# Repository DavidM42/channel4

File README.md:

# channel4

Analog broadcast television straight out of an ESP8266 pin, set up for black and white PAL TVs.

> ## This is cnlohr's work
>
> channel4 is a fork of **[cnlohr/channel3](https://github.com/cnlohr/channel3)** by Charles Lohr.
> The idea, the RF trick, the firmware, the 3D engine and the web interface are all his, and they are great.
> PAL line timing was also already in channel3, contributed there.
>
> This fork only adapts that work so it gives a solid picture on European black and white PAL sets, adds a few options around that, and explains how to build and flash it on a current Mac or Linux machine.
> The changes in this fork were made with the help of an AI coding assistant.
>
> If you have an NTSC TV, or you want color, use the original.

Solder a wire to the RX pin, flash the board, tune an old TV to channel E4 and watch a 3D demo that an ESP8266 is transmitting by toggling one pin.

## What is different from channel3

- **It broadcasts on European channel E4** (62.5 MHz) instead of US channel 3 (61.25 MHz), hence the name.
- **Black and white mode.** `MONOCHROME` leaves out all NTSC color information. The colors become clean shades of gray instead of hatching.
- **Optional bright border** for TVs that show dark screens as gray.
- **A steady PAL picture.** `NO_INTERLACE` stops the picture from jumping up and down by half a line, see [No interlacing](#no-interlacing).
- **Text from Home Assistant.** A text screen that you fill over WiFi, with a ready-made Home Assistant package.
- **A pause for the TV signal while a screen is sent.** The TV signal slows the board's WiFi down so much that a full screen can take a minute. With the pause it takes a few seconds, see [Faster screens](#faster-screens).
- **It stays on your WiFi.** channel3 switches back to its own access point at every start. This fork does not.
- **A relay that follows the screen.** With `RELAY_GPIO` a pin goes high whenever something is shown, for example to switch the TV on, see [A relay](#a-relay).
- **A silent start.** With `START_SILENT` the TV signal only starts when something asks for a screen, and a command stops it again, see [Signal only when needed](#signal-only-when-needed).
- **Updates over WiFi that check their work.** New firmware goes on over the network, is verified and only then takes over, see [Updating over WiFi](#updating-over-wifi).
- **A filter for the antenna pin.** The TV signal jams the board's own WiFi. Two small parts at the pin fix most of that, see [WiFi and the TV signal](#wifi-and-the-tv-signal).
- **PAL, black and white and no interlacing are switched on by default** in `user.cfg`.
- **A cable instead of an antenna.** A small board for the D1 Mini feeds the signal into the antenna socket of the TV, see [By cable instead of an antenna](#by-cable-instead-of-an-antenna).
- **Setup, build and flash instructions** for macOS and Linux, below.

Everything else, including the web interface and the demo screens, is channel3.

## What you need

- **An ESP8266 board with USB and 4 MB of flash.** A Wemos D1 Mini is what this was built and tested on.
- **A USB cable that carries data.** Many micro USB cables only charge. If no serial port shows up, try another cable first.
- **A piece of wire** for the antenna, 20 to 30 cm to start with. See [Antenna](#antenna).
- **A 100 ohm resistor and a 10 pF capacitor**, if you want to use WiFi while it broadcasts. See [The filter at the pin](#the-filter-at-the-pin).
- **An analog TV that receives VHF band I** (often labeled VHF-L or VL) in the B/G standard used in most of continental Europe.
- **A Mac or a Linux PC.** macOS on Apple Silicon was used for everything here, including flashing. On Linux the setup and build steps were checked on Ubuntu 24.04. Flashing from Linux was not tried, it is the same esptool command.

## Setup, build and flash

The whole thing is six steps. Steps 1 and 2 are only needed once.

### 1. Install the tools

You need `git`, `make` and `esptool` in version 4.8.1.

**macOS** (with [Homebrew](https://brew.sh))

```sh
xcode-select --install                 # git and make, skip if you have them
brew install pipx
pipx install esptool==4.8.1
pipx ensurepath                        # then open a new terminal
softwareupdate --install-rosetta       # Apple Silicon only, the compiler is an Intel program
```

On a Mac you also need the driver for the USB serial chip on the board. The Wemos D1 Mini uses a CH340, and its maker WCH has the driver here: https://www.wch-ic.com/downloads/CH34XSER_MAC_ZIP.html
Download it, run the installer, and allow it if macOS asks you to in System Settings under Privacy & Security. On the Mac this was built on, the board did not show up as a serial port before the driver was installed.

Boards with a different USB serial chip (a CP2102 for example) need that chip's driver instead.

**Linux** (Debian, Ubuntu and relatives, on a 64-bit Intel or AMD PC)

```sh
sudo apt-get install git make gcc python3 pipx wget
pipx install esptool==4.8.1
pipx ensurepath                        # then open a new terminal
sudo usermod -aG dialout $USER         # lets you use the serial port, log out and in again afterwards
```

Linux needs no driver for the CH340, it comes with the kernel.

Check that it worked. This should print `4.8.1`:

```sh
esptool.py version
```

The version matters. `brew install esptool` and a plain `pipx install esptool` give you esptool 5, and the build stops there with `Specify the --chip argument`. If you need esptool 5 for other things, see [Troubleshooting](#troubleshooting).

### 2. Get the compiler

The ESP8266 needs its own compiler, `xtensa-lx106-elf-gcc`.
Espressif publishes a ready-made one, so there is nothing to build.
Put it in `~/esp8266`:

**macOS**

```sh
mkdir -p ~/esp8266 && cd ~/esp8266
curl -LO https://dl.espressif.com/dl/xtensa-lx106-elf-macos-1.22.0-100-ge567ec7-5.2.0.tar.gz
tar xzf xtensa-lx106-elf-macos-1.22.0-100-ge567ec7-5.2.0.tar.gz
```

**Linux**

```sh
mkdir -p ~/esp8266 && cd ~/esp8266
wget https://dl.espressif.com/dl/xtensa-lx106-elf-linux64-1.22.0-100-ge567ec7-5.2.0.tar.gz
tar xzf xtensa-lx106-elf-linux64-1.22.0-100-ge567ec7-5.2.0.tar.gz
```

Check that it worked. This should print `5.2.0`:

```sh
~/esp8266/xtensa-lx106-elf/bin/xtensa-lx106-elf-gcc -dumpversion
```

### 3. Get the source

```sh
git clone --recursive https://github.com/DavidM42/channel4.git
cd channel4
```

`--recursive` matters. Most of the build lives in a submodule (`esp82xx`), and without it `make` finds nothing to do.
If you already cloned without it, run `git submodule update --init --recursive`.

### 4. Build

Run this in the `channel4` folder:

```sh
make clean ESP_ROOT="$HOME/esp8266" ESP_GCC_VERS=5.2.0 ESPTOOL_PY=esptool.py
make all   ESP_ROOT="$HOME/esp8266" ESP_GCC_VERS=5.2.0 ESPTOOL_PY=esptool.py
```

The three settings tell the build where the compiler from step 2 is, which version it is, and to use the esptool from step 1.

You will see a lot of compiler warnings. That is normal.
It worked if the last line says `Successfully created esp8266 image.` and these two files exist:

```
image.elf-0x00000.bin
image.elf-0x10000.bin
```

Always run `make clean` before `make all` after you change `user.cfg`. The build does not notice changes in that file by itself.

### 5. Flash

Plug the board in and find its serial port.

| | Command | Typical port |
|---|---|---|
| macOS | `ls /dev/cu.*` | `/dev/cu.wchusbserial10` |
| Linux | `ls /dev/ttyUSB*` | `/dev/ttyUSB0` |

If nothing like that is listed, see [Troubleshooting](#troubleshooting). On a Mac the usual reasons are the missing driver from step 1 or a USB cable that only charges.

Put it in a variable so the commands below can be copied as they are:

```sh
PORT=/dev/ttyUSB0      # use your own port here
```

**The first time**, write everything: the firmware, the web page, and the settings area the ESP8266 system software needs.

```sh
esptool.py --port "$PORT" -b 460800 write_flash -fm dio -fs 4MB \
  0x00000  image.elf-0x00000.bin \
  0x10000  image.elf-0x10000.bin \
  0x80000  web/page.mpfs \
  0x3FB000 esp82xx/toolchain/esp_nonos_sdk/bin/blank.bin \
  0x3FC000 esp82xx/toolchain/esp_nonos_sdk/bin/esp_init_data_default_v08.bin \
  0x3FE000 esp82xx/toolchain/esp_nonos_sdk/bin/blank.bin
```

**After that**, when you only rebuilt the firmware, the first two files are enough:

```sh
esptool.py --port "$PORT" -b 460800 write_flash -fm dio -fs 4MB \
  0x00000 image.elf-0x00000.bin \
  0x10000 image.elf-0x10000.bin
```

It worked if every file ends with `Hash of data verified.`

Three things worth knowing:

- **`-fs 4MB` is required.** Without it the firmware believes it has 1 MB of flash and looks for its settings in the wrong place.
- **These addresses are for 4 MB of flash**, which is what a D1 Mini has. `esptool.py --port "$PORT" flash_id` tells you what your board has. Other sizes were not tested here.
- **Use these commands instead of `make burn`.** The make targets leave out `-fs 4MB`, and they report success even when flashing failed.

### 6. Watch TV

1. Connect the wire to the pin labeled **RX** (GPIO3), best through [the filter](#the-filter-at-the-pin), and power the board from any USB supply.
2. Switch the TV to VHF band I (VHF-L, VL) and tune to channel E4, 62.5 MHz. On a set with a tuning wheel, turn slowly through the lower part of the band until the picture appears.
3. Set brightness so the background of a text screen is just black, then contrast so the text is crisp.

If `START_SILENT` is switched on in `user.cfg`, there is no picture until something asks for one. Join the board's WiFi network (see below) and open http://192.168.4.1/d/issue?CD to start the demo, or use the "Set Current" button on the web page.

The board also opens a WiFi network called `ESP_` followed by six characters. Join it and open http://192.168.4.1 for the web interface. Its "NTSC" button lets you freeze the demo on one screen, which makes adjusting the TV much easier.

### Updating over WiFi

Once a board runs this firmware and is on your network, new firmware can go on without USB:

```sh
python3 web/execute_reflash.py 192.168.1.50
```

That sends the two image files from the current folder. `make netburn IP=192.168.1.50`, with the same `ESP_ROOT=...` settings as in step 4, builds first and then does the same.

What happens:

1. It checks that the new firmware can go on this way, and whether the board already runs it.
2. It stops the TV signal, which disturbs the board's WiFi.
3. It puts both images into a spare part of the flash, reads them back and compares.
4. It tells the board to copy them over its firmware. The board checks them once more before it does.
5. It waits for the board to restart and reads its flash back.

Nothing on the board changes before step 4, and `--dry-run` stops before it.

**Step 4 takes about ten seconds. If the power fails in that time, the board does not start any more** and has to be flashed over USB.

The web page and the settings, the WiFi network among them, stay as they are.

## Options

All of these are lines in `user.cfg`. A `#` in front switches a line off.

| Line in `user.cfg` | What it does |
|---|---|
| `OPTS += -DPAL` | PAL timing: 625 lines, 50 fields per second. Off means NTSC. |
| `OPTS += -DMONOCHROME` | Black and white only. No colorburst, and the colors become shades of gray. |
| `OPTS += -DNO_INTERLACE` | PAL only. Draws both fields on the same TV lines, so the picture stands still. See [No interlacing](#no-interlacing). |
| `OPTS += -DFBH=264` | Full height PAL picture, 264 lines instead of 220. The web page then runs out of memory, see [Picture size and memory](#picture-size-and-memory). |
| `OPTS += -DWHITE_BORDER` | Paints the visible area left, right and above the picture bright instead of black. |
| `OPTS += -DBORDER_LEVEL=13` | How bright that border is. Only used together with `WHITE_BORDER`. |
| `OPTS += -DRELAY_GPIO=5` | A relay on that pin, on whenever something is shown. 5 is D1 on a D1 Mini. See [A relay](#a-relay). |
| `OPTS += -DSTART_SILENT` | No TV signal after power-up. It starts with the first text or demo command, see [Signal only when needed](#signal-only-when-needed). |

After changing any of them: `make clean`, `make all`, flash.

### Black and white only

On a black and white TV the NTSC color information only gets in the way. The colors show up as hatching, and the colorburst sits at a different level than black right where some TVs take their black reference.

With `MONOCHROME` there is no colorburst, and colors 0 to 15 become plain grays:

- 0 is black and 10 is white, as before.
- 2 and 8 are still the half black, half white ones that the sharp text uses.
- 3 to 7, 9 and 11 to 15 run from dark to bright.

A single pin can only be on or off, so only a few brightness levels come out clean. On channel E4 that is 8 grays between black and white, and some neighboring color numbers share a gray.

Both color tables live in `tablemaker/broadcast_tables.c`. The option picks one of them.

### No interlacing

A PAL picture is sent as two fields, and a TV draws the second one half a line below the first. channel3 sends the same picture in both, so everything jumps up and down by half a line, 25 times a second. On text that shows as a fine flicker, most of all on horizontal strokes.

With `NO_INTERLACE` the second field starts on a full line instead of half a line later, and the TV draws it on top of the first. Old home computers did the same. A field is then 312 lines instead of 312.5, and nothing of the picture is lost.

It is switched on in `user.cfg`. Take it out if your TV does not hold the picture with it. It only changes PAL, the NTSC signal is as it was.

### Bright border

Many small TVs, most black and white portables among them, do not hold their black level. A mostly dark picture like the text screens comes out as light gray text on a slightly darker gray.

Try the brightness and contrast controls of the TV first. That is usually enough.

If it is not, `WHITE_BORDER` gives the TV something bright to go by on every screen, without taking anything away from the picture. White (`BORDER_LEVEL=10`, the default) works best but glows on a small tube. With `MONOCHROME`, 13 is a light gray and a good place to start.

The lines below the picture always stay black. Bright lines running right up to the vertical sync made the whole picture bounce on the TV this was tried on.

### Picture size and memory

The picture is 220 lines high by default, also for PAL. It sits in the middle of the screen with a black strip above and below, and the text screen has 14 lines.

`FBH=264` fills a PAL screen and gives the text screen 17 lines. The 44 extra lines cost 5 kB of RAM, and the web page needs that memory. Measured with a clean WiFi link (RX pin silent, see [WiFi and the TV signal](#wifi-and-the-tv-signal)), loading the web page the way a browser does:

| Build | Page loads that completed | Lowest free memory |
|---|---|---|
| 220 lines (default) | 8 of 8 | 2.6 kB |
| 264 lines | 0 of 8 | 0.5 kB |

Single small requests, like the text commands from Home Assistant, worked with both: 30 of 30.

To see how much memory is free on your board, open `http://<board>/d/issue?I`. It is the last number.

### Signal only when needed

With `START_SILENT` the RX pin stays silent after power-up. The TV gets nothing, and the board's WiFi is not disturbed by the TV signal.

The signal starts when something asks for a screen, and stops on request:

| What | TV signal |
|---|---|
| `CT`, `CX` (text screen) and `CD` (demo) | on |
| The web page: its "Set Current" button for the screen, and "Upload As" for a color (`CO`, `CV`) | on |
| `CS` | off |

Send the commands as `http://<board>/d/issue?CS` and so on, see [The commands behind it](#the-commands-behind-it).

While the signal is off, no screens are drawn and the demo stands still. It carries on where it stopped, or from its first screen after `CD`. The part that makes the TV lines keeps running, so the picture is there at once when the signal comes on.

Without `START_SILENT` the signal is on from the start, as in channel3. `CS` and the commands that start the signal again work either way.

### A relay

With `RELAY_GPIO` the board switches a relay, for example one that powers the TV. The pin goes high for on.

| What | Relay |
|---|---|
| Every command that shows or changes something: `CT`, `CX`, `CD`, `CH`, `CG`, and `CO` and `CV` from the web page | on |
| `CR` | off |

Nothing else switches it off. `CS` and the pause while a screen is sent only stop the TV signal, the relay stays on through them. After power-up the relay is off with `START_SILENT`, and on without it, because the demo is showing then.

The number is the GPIO, not the label on the board. On a D1 Mini these are free:

| Label | `RELAY_GPIO` |
|---|---|
| D1 | 5 |
| D2 | 4 |
| D5 | 14 |
| D6 | 12 |
| D7 | 13 |

0, 2 and 15 work too, but the board reads those pins when it starts, and a relay on them can keep it from starting. The build stops with a message for any other number.

The pin gives 3.3 V and a few milliamps. That is enough for a relay module with its own transistor or optocoupler, not for a bare relay.

`RELAY_GPIO=5` is switched on in `user.cfg`. With a `#` in front of the line there is no relay, and the pin is left alone.

## Antenna

The antenna is a plain wire on the **RX** pin. For the picture alone that is all you need. If you also want WiFi to work, put [the filter](#the-filter-at-the-pin) between the pin and the wire.

- **Start with 20 to 30 cm**, laid near the TV or its aerial. That is enough across a table or a room.
- **A full quarter wave is about 1.15 m** on channel E4. Only go there if the short wire gives a snowy picture.
- **Do not go longer than you need.** The pin puts out a raw 80 MHz bit stream. Next to the TV channel it also produces copies on other frequencies, one of them around 97.5 MHz in the FM radio band. A longer wire radiates all of them further, and you have no license for any of them. Keep it on your desk.

For other channels, a quarter wave in meters is about 71 divided by the frequency in MHz.

**Keep the wire away from the board's own antenna**, the zigzag trace at the end of the ESP8266 module. The TV signal disturbs the board's WiFi, see [WiFi and the TV signal](#wifi-and-the-tv-signal).

**The antenna can block flashing.** RX is also the pin the USB chip uses to talk to the ESP8266. A wire hanging free is no problem. A wire that is plugged into a TV aerial socket, or touches grounded metal, holds the pin down, and esptool ends with `No serial data received`. Unplug the far end of the wire while you flash.

### By cable instead of an antenna

A TV with a socket for an outside antenna can get the signal by cable. Nothing is radiated then, and it no longer matters for the picture where the board and the TV stand. Here the picture rolled whenever the wire antenna lay next to large metal, a fridge or a microwave oven. By cable it stands still.

The pin puts out far more than a TV input wants, so a few parts go in between:

```
RX ──[ 100R ]──┬──[ 2k2 ]──┬──[ 1 nF to 1 µF ]──── tip of the plug
               │           │
             10 pF      [ 75R ]
               │           │
GND ───────────┴───────────┴────────────────────── sleeve of the plug
```

- **100 ohms and 10 pF** are [the filter at the pin](#the-filter-at-the-pin).
- **2.2 kΩ** takes the signal down. With 10 kΩ the picture was gone here, with 1 kΩ it rolled now and then.
- **75 ohms** to ground match the cable.
- **The capacitor** keeps DC from flowing between the board and the TV. On an electrolytic one the plus side goes towards the board.

[hardware/tv-shield](hardware/tv-shield/) has a board for these parts that sits on a D1 Mini. It has not been made yet.

Good to know:

- **Measure the socket first.** With the TV on, there should be about 0 V DC between its two contacts. This was tried on an IGS TV201, a small black and white portable with a 3.5 mm socket marked `EXT ANT 75Ω`.
- **Plug the cable in with both devices switched off.** They run from two power supplies.
- **The power supply of the board can get into the picture.** Bands and patterns went away here when the board ran from a battery. Try another USB power supply if you see them.
- **The WiFi of the board is still disturbed.** The cable made it better, not good. For screens of text, see [Faster screens](#faster-screens).

## WiFi and the TV signal

The TV signal on the RX pin disturbs the board's own WiFi. Without a filter the web page loads slowly or not at all, text commands get lost for minutes at a time, and the board's own network is hard to find and join.

### The filter at the pin

Two parts between the RX pin and the antenna wire fix most of it:

```
RX pin ───[ 100 ohm ]───┬─── antenna wire
                        │
                      10 pF
                        │
                       GND
```

- **100 ohms in series**, soldered as close to the RX pin as you can.
- **10 pF to ground**, from the wire side of the resistor.

The TV channel passes almost unchanged. What is held back is the part of the signal up in the 2.4 GHz band, which is what the wire radiates straight into the board's WiFi antenna.

Keep the wire itself away from the end of the board that has the WiFi antenna.

### What was measured

On a D1 Mini with a wire antenna on RX, on a home WiFi. All three columns are the same firmware:

| | RX pin silent | TV signal, no filter | TV signal, with filter |
|---|---|---|---|
| Small web requests answered correctly | 30 of 30 | 25 of 30 | 29 of 30 |
| The same with the text screen showing | not measured | 35 of 90, with one silence of 5 minutes | 85 of 90, no silences |
| Files of the web page, one after another (126 kB) | all complete, 1 second | first page loads, the scripts stall after 4 kB | all complete, 8 seconds |
| Web page loaded the way a browser does | 8 of 8 | did not complete | 5 of 8 |
| Board's own network shows up in WiFi scans | 10 of 10 | 8 of 16, with long gaps | not measured |

So the filter makes WiFi usable, but not as good as with the pin silent. Text commands get through, and the web page loads, sometimes only at the second try.

It is not the processor load and not memory. With the whole video generator running and only the pin switched off, WiFi was fine, and free memory was the same. Moving the board's network to another WiFi channel (6 or 11 instead of 1) did not cure it either.

## PAL

### What PAL means here

- **Timing is PAL.** 625 lines, 64 microseconds each, switched on with `-DPAL`. This part came with channel3.
- **There is no PAL color.** The color signal in the tables is NTSC. A PAL color set shows the picture in black and white, a black and white set never cared. With `MONOCHROME` the color signal is left out completely.
- **There is no sound.**
- **The picture is 232 x 220** in the sharp black and white mode that the text uses, and 116 x 220 with 16 colors or grays. A PAL screen has room for 264 lines, see [Picture size and memory](#picture-size-and-memory).
- **It is made for B/G sets**, the standard in most of continental Europe. French SECAM L sets use a different kind of modulation and will not show it. Sets that only have UHF, as many in the UK and Ireland do, cannot tune this low.

### Why 62.5 MHz

Channel E4 officially has its picture carrier at 62.25 MHz. This fork transmits 0.25 MHz above that, on purpose.

Every signal level is a fixed pattern of ones and zeros that repeats along the line. How often it repeats depends on the frequency:

| Frequency | Pattern repeats every | On the TV |
|---|---|---|
| 62.27 MHz, the closest possible to 62.25 | 176 bits | Coarse diagonal stripes over the whole picture |
| 62.5 MHz | 32 bits | Clean |
| 61.25 MHz, US channel 3 | 64 bits | What channel3 uses |

A long pattern beats against the carrier at a low frequency, and that shows as wide stripes. 62.5 MHz is exactly 25/32 of the 80 MHz bit clock, so the pattern is as short as it gets near E4. A TV tunes the quarter megahertz without complaint.

### Changing the channel

The frequency is set in `tablemaker/synthtables.c`:

```c
double MODULATION_Frequency = CHANNEL_E4;
```

Change it, then rebuild the tables and the firmware:

```sh
cd tablemaker && make synthtables && cd ..
make clean ESP_ROOT="$HOME/esp8266" ESP_GCC_VERS=5.2.0 ESPTOOL_PY=esptool.py
make all   ESP_ROOT="$HOME/esp8266" ESP_GCC_VERS=5.2.0 ESPTOOL_PY=esptool.py
```

Rules for picking a frequency:

- It has to be a multiple of 80/1408 MHz (about 0.0568 MHz), so that a whole number of cycles fits into the table.
- Prefer one that is a simple fraction of 80 MHz, for the reason above. In band I those are 47.5, 52.5, 57.5, 62.5 and 67.5 MHz (pattern of 32 bits) and 55 and 65 MHz (16 bits).
- `CHANNEL_3` gives you the original US channel 3 back.

Only 62.5 MHz and 62.27 MHz have been tried on a real TV here.

## Home Assistant

The firmware has a text screen that you fill over WiFi, one line at a time. Home Assistant can do that with its built-in `rest_command`, so there is nothing extra to install.

### 1. Put the board on your WiFi

Out of the box the board opens its own network. For Home Assistant to reach it, it has to join yours.

1. Join the board's `ESP_...` network and open http://192.168.4.1.
2. Open **Wifi Settings**, pick **Station**, enter the name (SSID) and password of your WiFi, and press **Change Settings**.
3. The board leaves its own network and joins yours. The first demo screen on the TV shows the address it got, on the line starting with `IP:`.
4. Tell your router to always give the board that address.

If the board cannot get onto your WiFi after a few tries, it opens its own network again so you can correct the settings.

If the page does not load completely, one address does the same as the form:

```
http://192.168.4.1/d/issue?W1%09YOUR-WIFI-NAME%09YOUR-PASSWORD
```

`%09` is what the firmware expects between the parts. Name and password together have to stay under about 60 characters. Like the form, this sends your password unencrypted over the board's open network.

Once the board is on your WiFi, open `http://<board>/d/issue?CW`. That makes sure the network is stored, so the board comes back to it after a power cut. The reply should start with `CW 1 1 1`.

### 2. Try it without Home Assistant

Open this in a browser, with the address of your board:

```
http://192.168.1.50/d/issue?CT00Hello+World
```

The TV switches to the text screen and shows `Hello World` on the top line. The browser shows `CT`.

### 3. Add the package to Home Assistant

1. Open [homeassistant/channel4.yaml](homeassistant/channel4.yaml) and replace `192.168.1.50` with the address of your board. It appears seven times.
2. Copy the file to `packages/channel4.yaml` in your Home Assistant configuration folder.
3. Make sure `configuration.yaml` loads packages:

   ```yaml
   homeassistant:
     packages: !include_dir_named packages
   ```

4. Restart Home Assistant.

Do not paste the contents of the file into `configuration.yaml` instead. That file usually already has a `script:` line, Home Assistant only keeps the last one it finds, and then either this script or all your own scripts are missing. The log shows `contains duplicate key "script"` when that happens.

The script is listed under its name, **TV: show message**. `script.channel4_message` is its entity ID.

### 4. Use it

The package gives you two scripts, seven commands and a switch.

| Name | What it does |
|---|---|
| `script.channel4_message` | Shows a message. Wraps long lines, handles line breaks, spells out umlauts. |
| `script.channel4_send` | Sets one line, or empties the screen if you give it no line. Tries up to three times if the board does not answer. The script above uses it. |
| `rest_command.channel4_line` | Sets one line and switches to the text screen. Line 0 is the top one. |
| `rest_command.channel4_clear` | Empties the text screen and switches to it. |
| `rest_command.channel4_demo` | Goes back to the demo. |
| `rest_command.channel4_stop` | Stops the TV signal. Any of the three above starts it again. |
| `rest_command.channel4_hold` | Pauses the TV signal while a screen is filled. Lines and clearing do not start it again. |
| `rest_command.channel4_show` | Ends the pause and shows the text screen. |
| `rest_command.channel4_relay_off` | Switches [the relay](#a-relay) off. The commands that show something switch it on again. |
| `input_boolean.channel4_pause_signal` | Switch it on and `script.channel4_message` pauses the TV signal while it sends, see [Faster screens](#faster-screens). |

For example, as the action of an automation:

```yaml
- service: script.channel4_message
  data:
    message: |-
      Washing machine
      is done
```

Or one line that changes while the rest stays:

```yaml
- service: rest_command.channel4_line
  data:
    line: 3
    text: "Living room {{ states('sensor.living_room_temperature') }} C"
```

### Faster screens

The TV signal on the RX pin disturbs the board's own WiFi. A screen is 15 requests, and with the signal on each of them can take seconds or get lost. The same 14 line screen took between 30 and 70 seconds here, and sometimes lines were missing.

With the signal off the board answers at once. So the message script can pause the signal for the time it sends: switch on **TV: pause signal while sending** (`input_boolean.channel4_pause_signal`). The TV shows snow for a moment, then the complete screen. In ten tries that took 3 to 6 seconds, and no line was lost.

What happens in between:

1. `CH` pauses the signal. This one command still has to get through with the signal on, so it gets six tries.
2. The screen is emptied and filled. These commands do not start the signal again while the pause lasts.
3. `CG` ends the pause. The signal comes back two tenths of a second later, so that the reply to `CG` gets out first.

If `CG` never arrives, the board ends the pause by itself, 8 seconds after the last command. If the pause command does not get through at all, the screen is sent the slow way.

The firmware has to know `CH` and `CG` for this. On a board with older firmware, leave the switch off.

The script waits a tenth of a second after every command. With the signal off the board turns down most requests that follow each other at once: 4 of 30 were answered without a gap, 30 of 30 with a tenth of a second.

### The commands behind it

These are ordinary channel3 custom commands, so anything that can open a web address can use them. Put them after `http://<board>/d/issue?`.

| Command | What it does | Reply |
|---|---|---|
| `CT` + two digits + text, like `CT03Hello` | Puts the text on that line and shows the text screen. No text empties the line. | `CT`, or `!CT` if there is no such line |
| `CX` | Empties all lines and shows the text screen. | `CX` |
| `CD` | Goes back to the demo, starting with its first screen. | `CD` |
| `CS` | Stops the TV signal. `CT`, `CX`, `CD` and the web page start it again. | `CS` |
| `CH` | Pauses the TV signal while a screen is filled. `CT` and `CX` do not start it again. The pause ends with `CG`, or by itself 8 seconds after the last of them. | `CH` |
| `CG` | Ends the pause and shows the text screen, two tenths of a second later. | `CG` |
| `CR` | Switches [the relay](#a-relay) off. Only in firmware built with `RELAY_GPIO`. | `CR` |
| `CW` | Stores the WiFi network the board is on, if it is not stored yet. | `CW`, then four numbers: mode now, mode stored (1 is on a network, 2 is its own access point), 1 if the stored network is the one in use, free memory |

The same commands also work as UDP packets to port 7878, without the address length limit below.

### Limits

- **36 characters per line.** Longer text is cut off. There are 14 lines (00 to 13), or 17 with `-DFBH=264`.
- **Web addresses are cut at 78 characters** by the firmware. That leaves 65 for the text after it has been encoded. Write spaces as `+`, which costs one character instead of the three of `%20`. The package does that for you.
- **The font only has plain ASCII.** German umlauts are spelled out (`ä` becomes `ae`, `ß` becomes `ss`). Any other special character becomes `?`.
- **The text is gone after a power cut.** The board starts with the demo again.
- **There is no password.** Everybody on your network can write on your TV.
- **A command can get lost.** With the text screen showing and [the filter](#the-filter-at-the-pin) fitted, 85 of 90 requests were answered correctly. Without the filter it was 35 of 90, with minutes of silence in between. `script.channel4_message` and `script.channel4_send` try each command up to three times. The `rest_command`s do not.

## Troubleshooting

| What you see | What to do |
|---|---|
| `make` does nothing, complains about missing files, or says the modules were not checked out | The submodule is missing. Run `git submodule update --init --recursive`. |
| `bad CPU type in executable` on a Mac | Install Rosetta: `softwareupdate --install-rosetta`. |
| The build stops with `Specify the --chip argument` | You have esptool 5. Install 4.8.1 as in step 1. If you want to keep 5, build with `ESPTOOL_PY="esptool.py --chip esp8266"` instead, that gives the same two files. Flashing with esptool 5 was not tried. |
| You changed `user.cfg` and nothing changed | Run `make clean` before `make all`. |
| No serial port appears when you plug the board in, on a Mac | Install the CH340 driver from step 1: https://www.wch-ic.com/downloads/CH34XSER_MAC_ZIP.html. If macOS asked to allow it, check System Settings under Privacy & Security, then unplug the board and plug it in again. If there is still no port, try another USB cable, many only charge. |
| No serial port appears when you plug the board in, on Linux | Try another USB cable, many only charge. On Ubuntu, the `brltty` package is known to grab these USB serial chips, remove it if you do not need it. |
| `Permission denied` on the port on Linux | Add yourself to the `dialout` group (step 1) and log in again. |
| `No serial data received` | The antenna is holding the RX pin down. Unplug its far end while flashing. See [Antenna](#antenna). |
| `No serial data received` with nothing connected to RX | The serial input of the board may be damaged. A board that still runs this firmware and is on your network can be updated without it, see [Updating over WiFi](#updating-over-wifi). |
| Flashing worked, but there is no picture and no WiFi network | Flash again with the long first-time command, including `-fs 4MB`. |
| The web page does not load | `web/page.mpfs` is not on the board. Flash with the long first-time command. |
| The web page loads slowly, or only shows "Introduction" and "NTSC" | The TV signal disturbs the board's WiFi. Fit [the filter at the pin](#the-filter-at-the-pin). With it the page can still need a second try. |
| The board's own network `ESP_...` is missing from the list, or joining it fails | Same cause, fit the filter. Without it the network comes and goes, try again a few times. |
| Text from Home Assistant does not arrive for minutes | Same cause, fit the filter. |
| The board is back on its own network after a restart | Put it on your WiFi again, then open `http://<board>/d/issue?CW`. The reply should start with `CW 1 1 1`. |
| The three `rest_command`s are there but `script.channel4_message` is missing | The file was pasted into `configuration.yaml`, which already has a `script:` line. Use it as a package, see [step 3](#3-add-the-package-to-home-assistant). In the list of scripts it is called "TV: show message". |
| Home Assistant warns `Setup of package 'channel4' failed: integration 'rest_command' has duplicate key 'url'` | The three commands are defined twice, in the package and somewhere else, usually a copy pasted into `configuration.yaml`. Remove that copy and restart. |
| Home Assistant cannot reach the board | Open `http://<board>/d/issue?CC` in a browser. If that does not show `CC`, the address is wrong or the board is not on your WiFi. Its address is on the first demo screen. |
| Text from Home Assistant ends in `?` or odd characters | The line was too long for the firmware's 78 character address limit. Use `script.channel4_message`, which keeps lines short enough. |
| Coarse diagonal stripes | The carrier frequency has a long bit pattern. See [Why 62.5 MHz](#why-625-mhz). |
| Text on a gray background instead of black | Turn the brightness of the TV down and the contrast up. If that is not enough, try `WHITE_BORDER`. |
| The picture rolls or bounces | Adjust V-hold on the TV to the middle of the range where the picture stands still. |

## How it works

Everything from here on is the original channel3 README. It describes NTSC and US channel 3. Where it says 61.25 MHz, this fork uses 62.5 MHz.

One demo screen is switched off in this fork: the "38x14 TEXT MODE" intro that came before the framebuffer copy test. Its text did not come out right on the test TV. The list of screens below is adjusted to match.

If you are looking for the kolumbus.fi NTSC/PAL mirror, see it here: https://cnlohr.github.io/channel3/ntsc_pal_frame_documentation/pal_ntsc_from_kolumbus_fi_pami1.html

### Background and RF

This uses the I2S Bus in the same way the esp8266ws2812i2s project does.  Difference is it cranks the output baud to 80 MHz.  We set up DMA buffers and let the CPU fill them as they pass through one line at a time.  The DMA interrupt fills in the buffers one word at a time.  The I2S bus shifts those buffers out at 80 MHz!

You may say "But nyquist says you can't transmit or receive frequencies at more than 1/2 the sample rate (40 MHz in this case).  To a degree that is true.  Some people thought it may be overtones, but what happens in reality something stranger happens.  Everything you transmit is actually mirrored around 1/2 the sample rate (40 MHz).  So, transmitting 60 MHz on an 80 MHz bitclock creates a waveform both at 60 as well as 20.  This isn't perfect.  Some frequencies line up to the 80 MHz well, others do not.

We store a bit pattern in the "premodulated_table" array.  This contains bitstreams for various signals, such as the "sync" level or "colorbust" level, or any of the visual colors.  This table's length of 1408 bits per color was chosen so that when sent out one bit at a time at 80 MHz, it works out to an even multiplier of the NTCS chroma frequency of 315.0/88.0 MHz, or 3.579545455 MHz.  You can calculate this by taking 1408/80MHz = 17.6us * 3.579545 MHz = 63 cycles, exactly.  Conveniently, it also works out to an even multiplier of 61.25 MHz, Channel 3's luma center.  17.6us * 61.25 MHz = 1078 cycles, exactly! When you modulate arbitrary frequencies, sometimes the cycles come out very uneven. 

In order to generate luma (the black and white portion) we modulate 61.25 MHz.  If we generate a strong signal, it is viewed as a very "dark", and a weak signal is a very "bright."  This means when we want to send out a sync pulse, we modulate it as loud as we can... when we want to modulate white, we put out barely any signal at all.  One thing you will notice is dot pour.  This is because the signal we are sending is so terrible.  The chroma signal is very dirty and has a repeating intensity pattern.  While the chroma lines up to the 1408 bit-wide repeating patten, the total number of pixels on the screen does not.  This causes the patterns created to roll down the screen.

In order to generate color, we need to modulate in a chroma signal, 3.579MHz above the baseband.  The chroma is synchronized by a colorburst at the beginning of each line.  This also sets the level for the chroma.  Then, during the line, we can either choose a "color" that has a high coefficient at the chroma level, or a low one.  This determines how vivid the color is.  We can change phase to change the color's hue.

This is basically a 1-bit dithering DAC, operating at a frequency below the nyquist, trying to encode luma and color at the same time.  Don't be surprised that the quality's terrible.

### Code Layout

Tables for handling the line-buffer state machine are (generated/stored?) in MayCbTables.h/c, and similar tables for creating the on-wire signal encoding are in synthtables.c.

Functions to set up the DMA transfers, refill the buffers when they become empty, and change what kind of line should be sent based on the framebuffer contents are in video_broadcast.c. These functions handle all of the modulation.  This sets up the DMA, and an interrupt that is called when the DMA finishes a block (equal to one line).  Upon completion, it uses CbTable to decide what function to call to fill in the line.  The interrupt fills out the next line for DMA which keeps going.

The framebuffer is updated by various demo screens located in user_main.c.

custom_commands.c contain the custom commands used for the NTSC-specific aspects.  Using the common websockets interface there are two added commands.  These include "CO" and "CV" which set the operation mode (CO) and allow users to change the modulation table from a web interface (CV).

### Demo screens

The following demo screens are available.  They normally tick through one after another (except ones after 10), unless the user disables this in the web browser.

### Screen Modes

1. Basic intro screen, shows IP address if available.
2. ESP8266 Features
3. Framebuffer copy test.  Beware, running this screen too long deliberately will cause a crash. <!-- channel3 original: "Intro to and completion of framebuffer copy test."  The intro screen ("38x14 TEXT MODE ...on 232x220 gfx") is commented out in user/user_main.c in this fork, the demo goes straight to the copy test. -->
6. Draw a bunch of lines... IN COLOR!
7. Matrix-based 3D engine demo.
8. Dynamic 3D mesh demo.
9. Pitch for this project's github.
10. Color screen with 16 color balls.
11. 4x4 color swatches, useful for when you're messing with colors in the web GUI.

### Web interface

The web interface is borrowing the web interface from esp8266ws2812i2s.  Power on the ESP, connect to it, then, point your web browser to http://192.168.4.1.  It has a new button "NTSC."  This gives you the option to allow demo to continue from screen to screen, or freeze at a specific screen.  You can specify the screen.  Additionally, for RF testing, you can jam a color.  Whenever the color jam is set to something 0 or above, it turns off all line drawing logic, and simply outputs that color continuously.  This will prevent TV sets from seeing it, however, you can see it on other RF equipment.

It also has an interactive Javascript webworker system that lets you write code to make a new color!  You can create a new bitstream that will be transmitted when a specific color is hit.  You can edit the code and it is effective as you type.  It automatically re-starts the webworker every time you change it.

You should only output -1 or +1 as that is all the ESP can output.  It will then run a DFT with a randomized window over a frequency area you choose.  Increase the DFT window, and it will increase your q (or precision).  Decrease, it decreases your q.  This is to help see how receivers like the TV really understand the signal and help illustrate how wacky this really is.

You can try it in your own browser using this link: http://cnlohr.github.io/channel3/web/page/index.html  Click NTSC and go to town.

### Rawdraw and 3D

For all the 3D and text, I'm using a new modified version of my "rawdraw" library ( http://github.com/cnlohr/rawdraw ) for 3D I'm using fixed point numbers, with 256 as the unit value, and the bottom 8 bits are the fractional component.

### PAL Modification

To allow for PAL broadcasts, the timings in the video_broadcast-library (formerly ntsc_broadcast) were modified. Since I only wanted to use this with a black an white TV, and PAL colour is actually quite complicated to do digitally, I didn't modify the broadcast_tables (synthtables.c). So the library broadcasts a PAL compliant B/W-Signal with NTSC Colour information (kind of like NTSC50).

To enable PAL broadcasting you need to enable ```OPTS += -DPAL``` in user.cfg. 

### Youtube video

Here is the original youtube video on this project:

Here is the new video (with COLOR):

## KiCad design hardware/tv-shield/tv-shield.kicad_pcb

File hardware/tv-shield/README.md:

# TV shield for the Wemos D1 Mini

A small board that sits on a Wemos D1 Mini and feeds the TV signal into the antenna socket of a TV by cable, instead of radiating it from a wire. It is 25.6 mm square, as wide as the D1 Mini, and has the same two rows of eight pins.

**This board has not been made or built yet.** The circuit on it is the one that works here with loose parts. The board itself passed KiCad's design rule check, and its pin order was compared with the D1 Mini part in KiCad's own library. Check the labels against your board before you order.

## The circuit

```
RX ──[ R3 100R ]──┬──[ R1 2k2 ]──┬──[ C1 ]──── TV, tip of the plug
                  │              │
               C2 10p         [ R2 75R ]
                  │              │
GND ──────────────┴──────────────┴──────────── TV, sleeve of the plug
```

- **R3 and C2** are [the filter at the pin](../../README.md#the-filter-at-the-pin) from the main README. R3 sits right next to the RX pin. They hold back the part of the signal that disturbs the board's own WiFi.
- **R1** takes the signal down to what a TV input expects and keeps the cable from loading the pin.
- **R2** matches the cable.
- **C1** keeps DC from flowing between the board and the TV.

## Parts

| Part | Value | Notes |
|---|---|---|
| R3 | 100 Ω | Part of the filter. Without the filter: a piece of wire in its place. |
| C2 | 10 pF | Part of the filter, ceramic, legs 2.5 mm apart. Without the filter: leave it out. |
| R1 | 2.2 kΩ | 1 kΩ if the picture is snowy. 10 kΩ was too much here, the picture was gone. |
| R2 | 75 Ω | 68 or 82 Ω work too. |
| C1 | 1 nF to 1 µF | Ceramic or electrolytic. It has three holes: the top one, marked `+`, and either the middle one (2.5 mm apart) or the bottom one (5 mm apart). The plus side of an electrolytic goes into the top hole. |
| J3 | TRU Components TC-9465728 | 3.5 mm socket, optional. For a cable with a plug at both ends. Conrad sells it as item 2366432. |
| Pins | 2 rows of 8, 2.54 mm | The ones that come with a D1 Mini. |

The resistors are ordinary quarter watt ones, laid flat.

**Without the socket:** solder the cable to the two holes at the bottom left instead, the inner wire to `TV` and the shield to `GND`.

**The socket was drawn from its data sheet** (drawing MJ-8435), not tried with a real one. Before you order more than a few boards, hold a socket against the first one. Its holes are round, 1.5 mm, not the slots of the data sheet, because not every board maker cuts slots that narrow. The flat legs fit through.

**The socket stands 0.3 mm over the edge of the board.** Its metal collar is wider than the body is high and would not clear the board otherwise.

## Which way round

The board goes on the D1 Mini with the line `WIFI ANTENNA THIS END` over the end that has the antenna, the zigzag trace on the metal can side. The socket then points the same way as the USB socket. Every pin is labeled, `RX` is the second one on the right.

The board ends before the antenna of the D1 Mini begins, so it does not cover it.

## Ordering

Send [tv-shield-gerbers.zip](tv-shield-gerbers.zip) to a board maker. Two layers, 1.6 mm thick, everything else as offered. The files in it:

| File | What it is |
|---|---|
| `.gtl`, `.gbl` | Copper, top and bottom. The bottom is one ground area. |
| `.gts`, `.gbs` | Solder mask |
| `.gto`, `.gbo` | Printing |
| `.gm1` | Outline |
| `.drl` | Holes |

## Having it assembled

Two more files are for a service that also solders the parts:

| File | What it is |
|---|---|
| [tv-shield-bom.csv](tv-shield-bom.csv) | The parts, with the column names JLCPCB reads. Other services take the same file. |
| [tv-shield-positions.csv](tv-shield-positions.csv) | Where each part goes, measured to the middle of its legs. |

What to know before you ask for a price:

- **Only C1 has an LCSC number**, a 1 µF electrolytic capacitor (C841716), the kind this circuit was tried with. It was looked up, stock and price were not. Its legs are 2 mm apart and go into the top and the middle hole, plus side at the top.
- **The socket is the one from Conrad** and has no LCSC number. A service would have to get it from you, or you solder it in yourself.
- **The three resistors and the 10 pF capacitor have none.** I did not find these exact values as through-hole parts in a search from outside the shop. JLCPCB lets you pick a part for such a line after the upload. The description in the list says what to look for.
- **The pin rows are in neither file.** Which way round they go depends on how you stack the boards, and a D1 Mini comes with pins. You solder those yourself.
- **Every part here is through-hole.** Services charge more for those than for surface-mount parts, often per solder joint. For a batch that is assembled for you, compare with [the surface-mount version](../tv-shield-smd/) of this board.
- **The positions were not checked against a service's preview.** Look at the preview they show before you order, and turn a part there if it sits the wrong way.

## Changing it

The board is drawn by [make_board.py](make_board.py), all positions and the parts list are in it. It needs the Python that comes with KiCad 9. Without KiCad installed, the container does it:

```sh
docker run --rm --platform linux/amd64 -v "$PWD":/work -w /work kicad/kicad:9.0 sh -c '
  python3 make_board.py tv-shield.kicad_pcb &&
  kicad-cli pcb drc --severity-all --exit-code-violations tv-shield.kicad_pcb &&
  kicad-cli pcb export gerbers --layers F.Cu,B.Cu,F.SilkS,B.SilkS,F.Mask,B.Mask,Edge.Cuts --subtract-soldermask -o gerbers/ tv-shield.kicad_pcb &&
  kicad-cli pcb export drill --format excellon --excellon-units mm -o gerbers/ tv-shield.kicad_pcb'
```

`tv-shield.kicad_pcb` opens in KiCad 9 as well, if you would rather move things by hand.

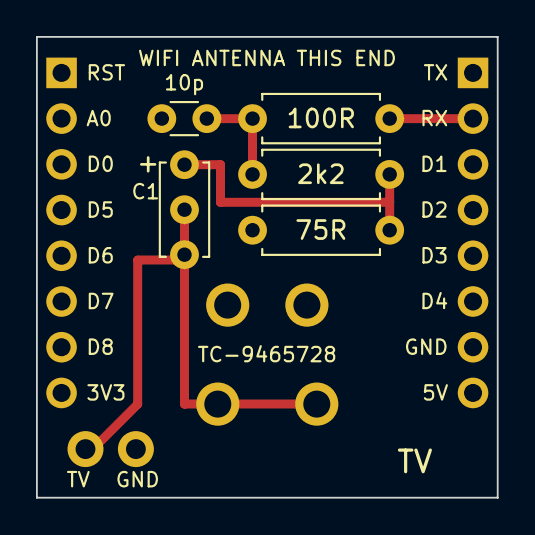
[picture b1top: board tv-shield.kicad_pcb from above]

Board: 2 copper layers, 25.6 x 25.6 mm, 9 parts (0 on the bottom side), 5 nets.

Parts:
C1: 1n to 1u; C_Disc_D5.0mm_W2.5mm_P5.00mm
C2: 10p; C_Disc_D3.0mm_W1.6mm_P2.50mm
J1: D1 Mini left row; PinHeader_1x08_P2.54mm_Vertical
J2: D1 Mini right row; PinHeader_1x08_P2.54mm_Vertical
J3: TC-9465728
J4: cable
R1: 2k2; R_Axial_DIN0207_L6.3mm_D2.5mm_P7.62mm_Horizontal
R2: 75R; R_Axial_DIN0207_L6.3mm_D2.5mm_P7.62mm_Horizontal
R3: 100R; R_Axial_DIN0207_L6.3mm_D2.5mm_P7.62mm_Horizontal

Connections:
FILTERED: C2.1, R1.1, R3.2
GND: C2.2, J2.7, J3.R, J3.S, J4.2, R2.2
MID: C1.1, R1.2, R2.1
RX: J2.2, R3.1
TV: C1.2, J3.T, J4.1

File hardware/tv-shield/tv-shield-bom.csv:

Comment,Designator,Footprint,LCSC Part #,Quantity,Description,Manufacturer,Manufacturer Part #
100R,R3,Axial 7.62 mm,,1,"Resistor, 100 ohm, 1/4 W, axial, 6.3 x 2.5 mm, 1 % or 5 %",,
2k2,R1,Axial 7.62 mm,,1,"Resistor, 2.2 kohm, 1/4 W, axial, 6.3 x 2.5 mm, 1 % or 5 %",,
75R,R2,Axial 7.62 mm,,1,"Resistor, 75 ohm, 1/4 W, axial, 6.3 x 2.5 mm, 1 % or 5 %",,
10p,C2,Radial 2.54 mm,,1,"Ceramic capacitor, 10 pF, 50 V, NP0, legs 2.54 mm apart",,
1u,C1,Radial 5 mm,C841716,1,"Electrolytic capacitor, 1 uF, 50 V, 5 x 11 mm, legs 2 mm apart, plus side into the hole marked +",Nippon Chemi-Con,EKY-500ELL1R0ME11D
3.5 mm socket,J3,TC-9465728,,1,"3.5 mm stereo socket, through-hole, right angle, Conrad 2366432",TRU Components,TC-9465728
